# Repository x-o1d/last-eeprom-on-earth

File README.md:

# last-eeprom-on-earth

a website developed by millions of beings with values,

live version hosted at:

https://aragalaya.online
http://aragalaya.online:5555
http://aragalaya.online:5555/index555.html

all three links point to the same file.

go to a link and a revolutionary army agent will come to where you are, and they will start training you for the mission of creating a just world where you wont have to raise your hand or sell your soul to be succesful. 

# this github repository isn't indexed on google but is indexed on search engines like duckduckgo, figure out why and you'll win a cookie.

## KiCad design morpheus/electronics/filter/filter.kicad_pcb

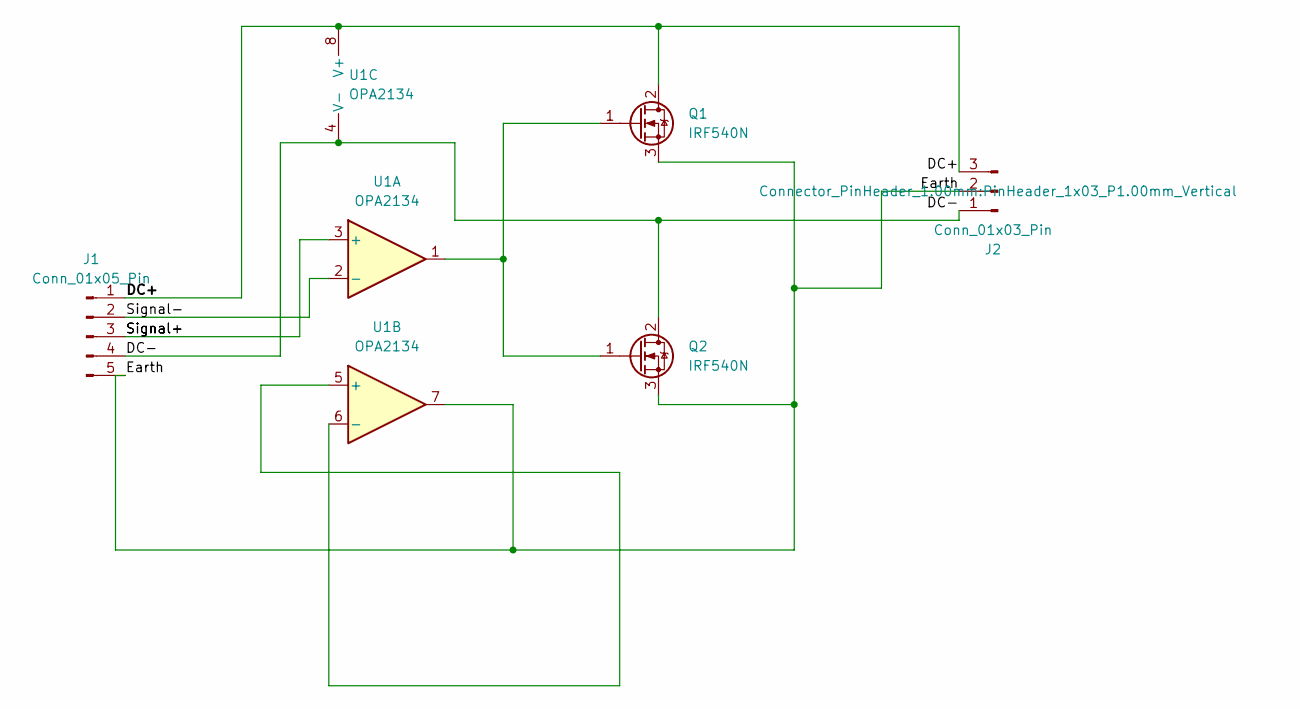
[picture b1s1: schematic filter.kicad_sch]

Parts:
J1: Conn_01x05_Pin; PinHeader_1x05_P1.00mm_Vertical
J2: Conn_01x03_Pin; PinHeader_1x03_P1.00mm_Vertical
Q1, Q2: IRF540N; TO-220-3_Vertical
U1: OPA2134; DIP-8_W7.62mm

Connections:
/DC+: J1.1, J2.3, Q1.2 (D), U1.8 (V+)
/DC-: J1.4, J2.1, Q2.2 (D), U1.4 (V-)
/Earth: J1.5, J2.2, Q1.3 (S), Q2.3 (S), U1.7
/Signal+: J1.2, J1.3, U1.2 (-), U1.3 (+)
unnamed: Q1.1 (G), Q2.1 (G), U1.1
unnamed: U1.5 (+), U1.6 (-)

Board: 2 copper layers, 5 parts (0 on the bottom side), 6 nets, no tracks yet.

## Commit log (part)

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2025-11-23 Update README.md
    update readme
2025-11-23 Update README.md
    mission
2025-11-29 Update README.md
    why this repository isn't indexed on google
2025-11-30 add og tags
2025-12-07 add abuses html
2025-12-07 abuses .matrix file
2026-02-03 beta
2026-02-04 beta 1
2026-02-04 file structure
